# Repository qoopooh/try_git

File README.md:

# Sandbox Repository
Welcome to the Sandbox Repository! This repository is designed for testing purposes and contains code snippets and projects in multiple programming languages. Please note that the code in this repository is purely for experimental and educational purposes, and should not be considered as production-ready or reliable.

## Purpose
The main purpose of this repository is to provide a safe environment for testing and exploring different programming languages. It serves as a playground for developers to experiment with various language features, algorithms, libraries, and frameworks without any constraints. However, please keep in mind that the code here is not intended for production use and should be used solely for educational and learning purposes.

## Contents
The repository consists of code examples and projects in different programming languages, including but not limited to:

* Java
* Python
* JavaScript
* C++
* *Go
* Rust

Each language has its own directory within the repository, containing code snippets, sample projects, and README files specific to that language. Feel free to explore the different directories and files to learn about the specific language or project you're interested in.

## Usage
To make the most of this repository, you can clone it to your local machine using the following command:

```
git clone https://github.com/qoopooh/try_git.git
```

Once you have the repository cloned, you can navigate to the desired programming language directory and explore the available code. You are encouraged to modify and experiment with the code to gain a better understanding of the language or specific concepts.

## Contributing
Contributions to this repository are not actively sought or expected. However, if you have any valuable code snippets or small projects that you believe would benefit the community, you can submit a pull request. Please ensure that your contribution aligns with the purpose of this repository and clearly documents any relevant information in the corresponding README file.

## Disclaimer
Please be aware that the code in this repository is not intended for production use. It may contain errors, bugs, or security vulnerabilities. Using any code from this repository in a production environment is strongly discouraged. The contributors of this repository shall not be held responsible for any damages or consequences resulting from the usage of the code provided.

## License
The code in this repository is provided under the MIT License. By using this code, you agree to the terms and conditions outlined in the license file.

## Contact
If you have any questions or suggestions regarding this repository, please feel free to open an issue or contact the repository maintaine. However, please keep in mind that this repository is primarily for testing purposes, and support may be limited.

Happy sandboxing and exploring different programming languages!

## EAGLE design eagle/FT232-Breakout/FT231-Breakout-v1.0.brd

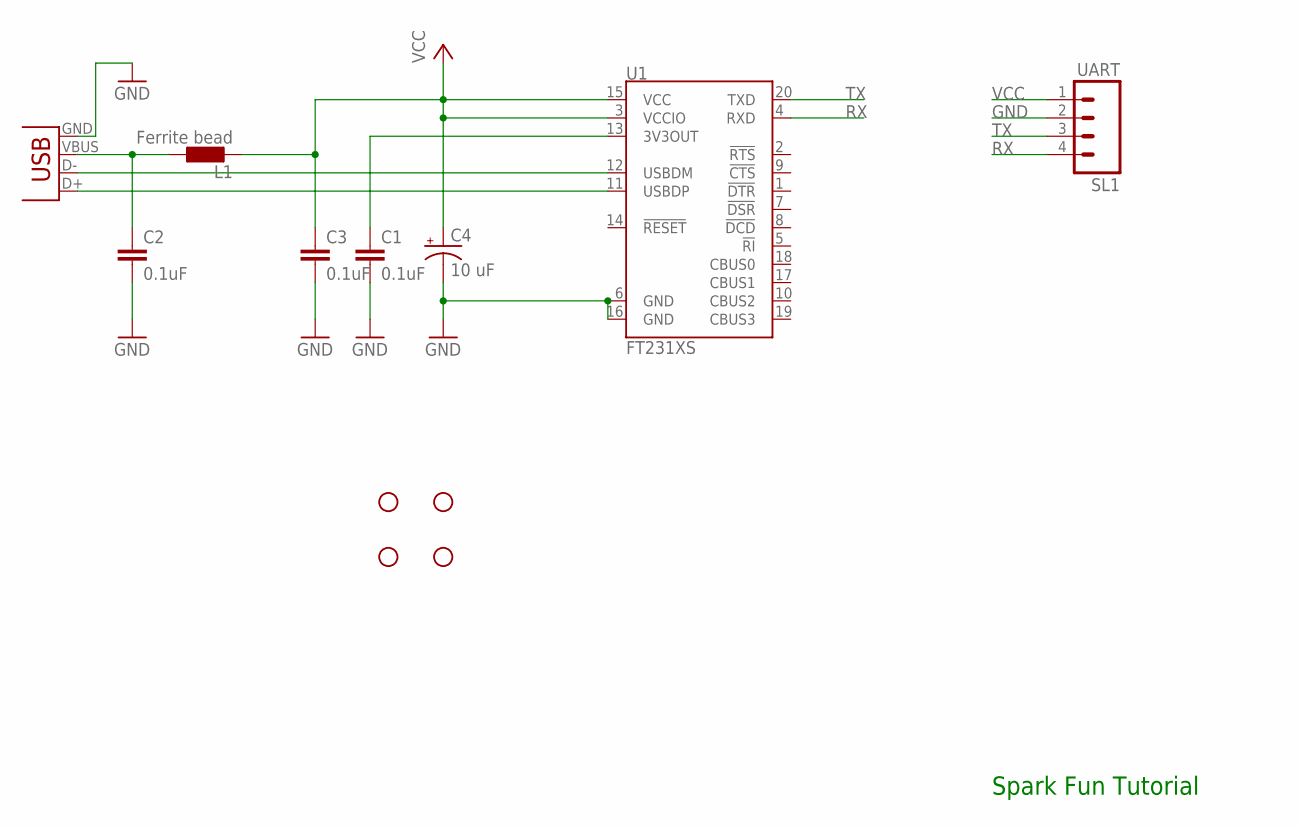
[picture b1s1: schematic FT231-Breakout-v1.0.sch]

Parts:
C1, C2, C3: 0.1uF; 0603-CAP
C4: 10 uF; EIA3216
JP1: USB-B; USB-B-PTH
L1: Ferrite bead; L1812
SL1: UART; 04P
STANDOFF1, STANDOFF2, STANDOFF3, STANDOFF4: STAND-OFF
U1: FT231XS; SSOP20_L

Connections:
GND: C1.2, C2.2, C3.2, C4.C (-), JP1.GND, SL1.2, U1.6 (GND), U1.16 (GND)
unnamed: JP1.D-, U1.12 (USBDM)
unnamed: JP1.D+, U1.11 (USBDP)
unnamed: C1.1, U1.13 (3V3OUT)
unnamed: C2.1, JP1.VBUS, L1.1
RX: SL1.4, U1.4 (RXD)
TX: SL1.3, U1.20 (TXD)
VCC: C3.1, C4.A (+), L1.2, SL1.1, U1.3 (VCCIO), U1.15 (VCC)

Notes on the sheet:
Spark Fun Tutorial

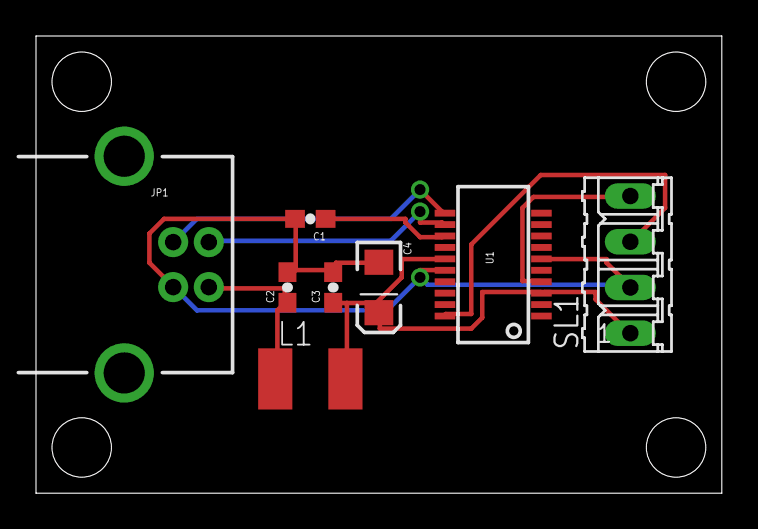
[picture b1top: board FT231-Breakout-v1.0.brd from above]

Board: 2 copper layers, 38.1 x 25.4 mm, 12 parts (0 on the bottom side), 8 nets.

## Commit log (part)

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2014-01-09 icon for mac
2014-01-09 win ico
2014-01-09 No Windows7 Desktop Icon
2014-01-09 Prepare next version
2014-01-10 Prepare NVCMDCS56 to Bootloader
2014-01-10 revise baud
2014-01-15 Publish H:\svn\git\try_git\chrome\aia20plnp
2014-01-15 change 128px
2014-01-20 prepare article search
2014-01-27 prepare update transaction
2014-01-28 can connect to aaebio, but not erpraid
2014-01-28 resized image is on python path
2014-01-28 release V1.0
2014-01-29 prevent SQL injection
2014-01-30 apk on Mac
    Generate Android.apk with
    /Users/ads/git/try_git/qt5/android_release.keystore
2014-01-30 release 0.6 - match screen for cca
2014-02-04 Create GAE with java - https://developers.google.com/appengine/docs/java/gettingstarted/creating - https://developers.google.com/appengine/docs/java/tools/ant - run on http://localhost:8080/guestbook
2014-02-04 The Guestbook Form - and log https://developers.google.com/appengine/docs/java/gettingstarted/usingjsps
2014-02-04 prepare for https://developers.google.com/appengine/docs/java/gettingstarted/usingdatastore
2014-02-06 create link and images
2014-02-06 add more condition to put -
2014-02-07 backup match code
2014-02-09 backup update
2014-02-10 Release V1.1 - Search for each detail e.g., Match Code, Description 1 - Show photo and datasheet on infomation page - Show unit
2014-02-13 prepare unikware killer
    Run on Windows only
2014-02-18 copy from C:\Qt\4.7.4\examples\desktop\systray
2014-02-18 show icon
2014-02-18 close usr-tcp-232 setup
2014-02-18 bug on win7 git
2014-02-19 icon exe
2014-02-19 Release Unikware Monitor V1.0
2014-02-19 Release Unikware Monitor V0.1
2014-02-21 If it's not real article number
2014-02-22 http://www.cocos2d-x.org/wiki/Chapter_6_-_How_to_Play_Music_and_Sound_Effect
    I heard nothing
2014-02-26 exit tray after half an hour
2014-03-03 connect mysql - http://codeinthehole.com/writing/how-to-set-up-mysql-for-python-on-ubuntu/
2014-03-03 ready to release http://aae014/unikmon/
2014-03-04 move aia to utils
2014-03-06 thumbnailing jpg files on current folder
2014-03-07 create nanosoft export
2014-03-15 remove comman on nanosoft format
2014-03-18 Last one from Josef
2014-03-26 FTC 0.7
    name + status command
2014-03-31 ignore spbtv_0.0.5b.zip
2014-04-10 debug article-checking
2014-04-14 outer join
2014-04-17 new tyre stock
2014-04-17 insert production stock
2014-04-21 try new tyre instock
2014-04-23 test mysql server on aae014 we need: - GRANT ALL ON et_service.* TO berm@% IDENTIFIED BY berm; - sudo vi /etc/mysql/my.cnf - bind-address = 192.168.1.44
2014-04-30 qsqlite4.dll, the right one is 467KB
    ‎Friday, ‎02 ‎September, ‎2011, ‏‎00:48:50
    467 KB (478,720 bytes)
    4.7.4
2014-04-30 remove
    adding mistake
2014-05-05 finish REM_XXX_STOCK
2014-05-09 Release TireTagLogger V1.00
    update report
2014-05-13 create STM32F103RB project
2014-05-13 copy from /Users/macmini/Library/Rowley Associates Limited/CrossWorks for ARM/v3/packages/targets/STM32/include
2014-05-23 copy from url = git://github.com/leaflabs/maple-bootloader.git
2014-05-28 query version from manifest
2014-05-31 test java applet - compile with javac - run html with appletviewer
2014-05-31 PLL x6 = 48MHz
2014-06-01 mvn archetype:generate -DarchetypeGroupId=org.apache.maven.archetypes -DgroupId=com.berm.motor -DartifactId=mo tor
2014-06-02 generate
2014-06-03 mvn exec:java - change pom.xml to execute app from mvn - the other way is "java -cp target/motor-1.0-SNAPSHOT.jar com.berm.motor.App"
2014-06-03 add combo box
2014-06-28 prepare serial communication
2014-06-30 set width of article column to 10%
2014-07-03 - add year from yy to yyyy - cancel generate if we don't have revision
2014-07-09 new token (5 minutes ago)
2014-07-09 remove u
2014-09-02 show OLED message
2014-09-03 prevent removing image with "-thumb"
2014-09-07 Prepare quiz http://wiki.quantsoftware.org/index.php?title=Compinvesti-prog-quiz
2014-09-25 bash bug
2014-09-25 Execute jar file from "mvn exec:java"
2014-09-26 show message dialog
2014-09-26 Set default value and shrink window
2014-09-26 Copy pom.xml from Area
2014-09-30 Test bash shell shock
2014-10-01 Default article is 780
2014-10-04 Prepare for Java7Essentials example
2014-10-05 cannot find SerialPort
2014-10-28 https://code.google.com/p/guava-libraries/wiki/UseGuavaInYourBuild
2014-10-28 solved "/home/berm/git/tg/java/Gluava/src/test/java/com/berm/swguava/AppTest.java:[84,17] generics are not supported in -source 1.3"
2014-10-29 Remove git from AAE014
2014-12-17 Add Gradle Template
2015-02-11 Completed Amazon Receipt Verification Service API - Use https://appstore-sdk.amazon.com/version/1.0/verifyReceiptId/developer/ instead
2015-02-23 Compile pass with gradle 2.3 http://gradle.org/downloads
2015-02-23 Test all variation
2015-03-30 - Get table data (td)
2015-04-28 Can count number
2015-04-28 - Show software/hardware version
2015-04-28 prepare command
2015-07-02 - Finish http://tour.golang.org/basics/ - http://obahua.com/setup-vim-for-go-development/
2015-07-28 - Update aia fund output as string
2015-07-28 - Python load json - Try insert database
2015-07-28 - Run aialog on pi /etc/cron.hourly
2015-07-28 uwsgi --http :8000 --wsgi-file test.py
2015-07-28 - Run django pub app
2015-07-29 - Compare last price before update
2015-07-30 - Fixed aialog checking price changed
2015-08-05 - Test flask template
2015-08-05 - Run uwgsi with uwgx.ini
2015-08-09 - Add uwgx config
2015-08-10 python manage.py startapp myapp
2015-08-10 django add index page
2015-08-13 - email validation works only first time
2015-08-13 - Prepare bootstrap for eurosoft
2015-08-13 - MSSQL on yosemite
2015-08-16 web.py session example does not work http://webpy.org/sessions/simpleexample
2015-08-17 - Use web.py session to keep usr/passwd and eid - Using session with reloader (debug mode)
2015-08-18 - Add jquery mobile template on flask
2015-08-19 - Cleanup duplicated rows in Eurosoft
2015-08-21 - Run spark with maven2
2015-08-22 - Test spring with gradle ./gw run (http://localhost:8080/greeting) example: http://spring.io/guides/gs/serving-web-content/
2015-08-23 - Deploy war with thymeleaf on pi - Add second parameter to greeting
2015-08-23 - Use th:each for spring mysql on pi
2015-08-23 - create spring price page
2015-08-25 - Sample sqlite on jdbc
2015-08-25 - Add link to main page
2015-08-27 - Move MySQLdb to pymysql - Update debug / logger
2015-08-28 - Get Started: spring-boot gw run http://localhost:8080
    java -jar build/libs/boot-0.1.jar
2015-08-30 - Decode some utf from python - Test sqlalchemy
2015-08-30 foriegned key
2015-09-01 - Update help / do not remove original image
2015-09-01 - Test python version on docker
2015-09-02 - comments
2015-09-02 - java mysql can print utf8 if database is utf8 as well
2015-09-05 - create database on lmde - simplify password
2015-09-06 - corrected position order
2015-09-11 - Set unique username
2015-09-21 Add MeterUse data
2015-11-17 Simple angular
2015-11-17 HTTP get to table
2015-12-11 Test node gandi xmlrpc
2016-01-22 Fixed changing back aia database name (test)
2016-05-06 Improve sending udp
2016-05-27 Monitor serial data from BT module
2016-05-27 Set name of BT
2016-06-06 nginx with pip install docker-compose
2016-06-07 Docker compose
2016-06-20 Docker nodemon
2017-07-26 Run on miniSTM32F103R__-EK board
    - make clean && make CFLAGS=-DSTM32F103R && make flash
    - Use 2 leds
    - Disable usb
2017-10-02 Arduino send On / Off commands
    - Based on SerialEvent
    - Baud 115200
    - End with '\n'
2018-03-04 medium: manage header/footer tags and ids
2018-03-25 medium: remove addthis
2018-04-04 Limit to 1 thread
2018-11-24 unikware_launcher v0.10
    - set timeout to 30 minutes
2020-02-11 Bump django in /python/django/django15_project/my_django15_project
    Bumps [django](https://github.com/django/django) from 1.5.12 to 1.11.28.
    - [Release notes](https://github.com/django/django/releases)
    - [Commits](https://github.com/django/django/compare/1.5.12...1.11.28)
2020-02-15 HF reader
    - Remove django
2020-02-15 Bump ejs from 0.8.3 to 3.0.1 in /serial
    Bumps [ejs](https://github.com/mde/ejs) from 0.8.3 to 3.0.1.
    - [Release notes](https://github.com/mde/ejs/releases)
    - [Changelog](https://github.com/mde/ejs/blob/master/CHANGELOG.md)
    - [Commits](https://github.com/mde/ejs/commits/v3.0.1)
2020-02-15 Bump django from 1.11.5 to 1.11.28 in /docker/django/hello
    Bumps [django](https://github.com/django/django) from 1.11.5 to 1.11.28.
    - [Release notes](https://github.com/django/django/releases)
    - [Commits](https://github.com/django/django/compare/1.11.5...1.11.28)
2020-06-05 Bump django from 1.8.1 to 1.11.29 in /docker/django/dev/web
    Bumps [django](https://github.com/django/django) from 1.8.1 to 1.11.29.
    - [Release notes](https://github.com/django/django/releases)
    - [Commits](https://github.com/django/django/compare/1.8.1...1.11.29)
2020-06-06 remove hello django
2020-10-13 Bump junit from 3.8.1 to 4.13.1 in /java/BasicSwing
    Bumps [junit](https://github.com/junit-team/junit4) from 3.8.1 to 4.13.1.
    - [Release notes](https://github.com/junit-team/junit4/releases)
    - [Changelog](https://github.com/junit-team/junit4/blob/main/doc/ReleaseNotes4.13.1.md)
    - [Commits](https://github.com/junit-team/junit4/commits/r4.13.1)
2020-10-13 Bump junit from 3.8.1 to 4.13.1 in /java/st110
    Bumps [junit](https://github.com/junit-team/junit4) from 3.8.1 to 4.13.1.
    - [Release notes](https://github.com/junit-team/junit4/releases)
    - [Changelog](https://github.com/junit-team/junit4/blob/main/doc/ReleaseNotes4.13.1.md)
    - [Commits](https://github.com/junit-team/junit4/commits/r4.13.1)
2020-10-13 Bump junit from 3.8.1 to 4.13.1 in /java/motor
    Bumps [junit](https://github.com/junit-team/junit4) from 3.8.1 to 4.13.1.
    - [Release notes](https://github.com/junit-team/junit4/releases)
    - [Changelog](https://github.com/junit-team/junit4/blob/main/doc/ReleaseNotes4.13.1.md)
    - [Commits](https://github.com/junit-team/junit4/commits/r4.13.1)
2020-10-13 Bump junit from 3.8.1 to 4.13.1 in /java/CreditCardVerifier
    Bumps [junit](https://github.com/junit-team/junit4) from 3.8.1 to 4.13.1.
    - [Release notes](https://github.com/junit-team/junit4/releases)
    - [Changelog](https://github.com/junit-team/junit4/blob/main/doc/ReleaseNotes4.13.1.md)
    - [Commits](https://github.com/junit-team/junit4/commits/r4.13.1)
2021-04-12 Create time table cron
2021-04-12 Do not check sprinkler at night
2021-06-04 Set LED_BUILTIN
2021-06-05 Send location via lora
2021-06-06 T-Beam sleep mode
2022-07-28 Use module github.com/qoopooh/linenotify
    - time CGO_ENABLED=0 GOOS=linux GOARCH=arm GOARM=7 go build -ldflags="-s -w"
2022-12-27 Use github.com/qoopooh/linenotify Use LINE_NOTIFY_PREFIX https://www.tutorialspoint.com/lua/lua_coroutines.htm
2023-02-26 Simple http server (chat app)
    - Prepare login page
    - go test -cover
    - Test OpenAI API on golang
2023-04-21 Update lib
2023-04-23 TypeScript tutorial
    - https://www.youtube.com/watch?v=30LWjhZzg50
2023-05-28 README.md
2023-10-07 User-defined subroutines
2024-03-25 Bump express from 3.2.0 to 4.19.2 in /jqm
    Bumps [express](https://github.com/expressjs/express) from 3.2.0 to 4.19.2.
    - [Release notes](https://github.com/expressjs/express/releases)
    - [Changelog](https://github.com/expressjs/express/blob/master/History.md)
    - [Commits](https://github.com/expressjs/express/compare/3.2.0...4.19.2)
    ---
    updated-dependencies:
2024-05-02 Bump ejs from 3.1.7 to 3.1.10 in /serial
    Bumps [ejs](https://github.com/mde/ejs) from 3.1.7 to 3.1.10.
    - [Release notes](https://github.com/mde/ejs/releases)
    - [Commits](https://github.com/mde/ejs/compare/v3.1.7...v3.1.10)
    ---
    updated-dependencies:
    - dependency-name: ejs
2024-05-09 linux amd64 asm

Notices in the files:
parts and their libraries:
SparkFun-DigitalIC: Licensing: CC v3.0 Share-Alike You are welcome to use this library for commercial purposes.
